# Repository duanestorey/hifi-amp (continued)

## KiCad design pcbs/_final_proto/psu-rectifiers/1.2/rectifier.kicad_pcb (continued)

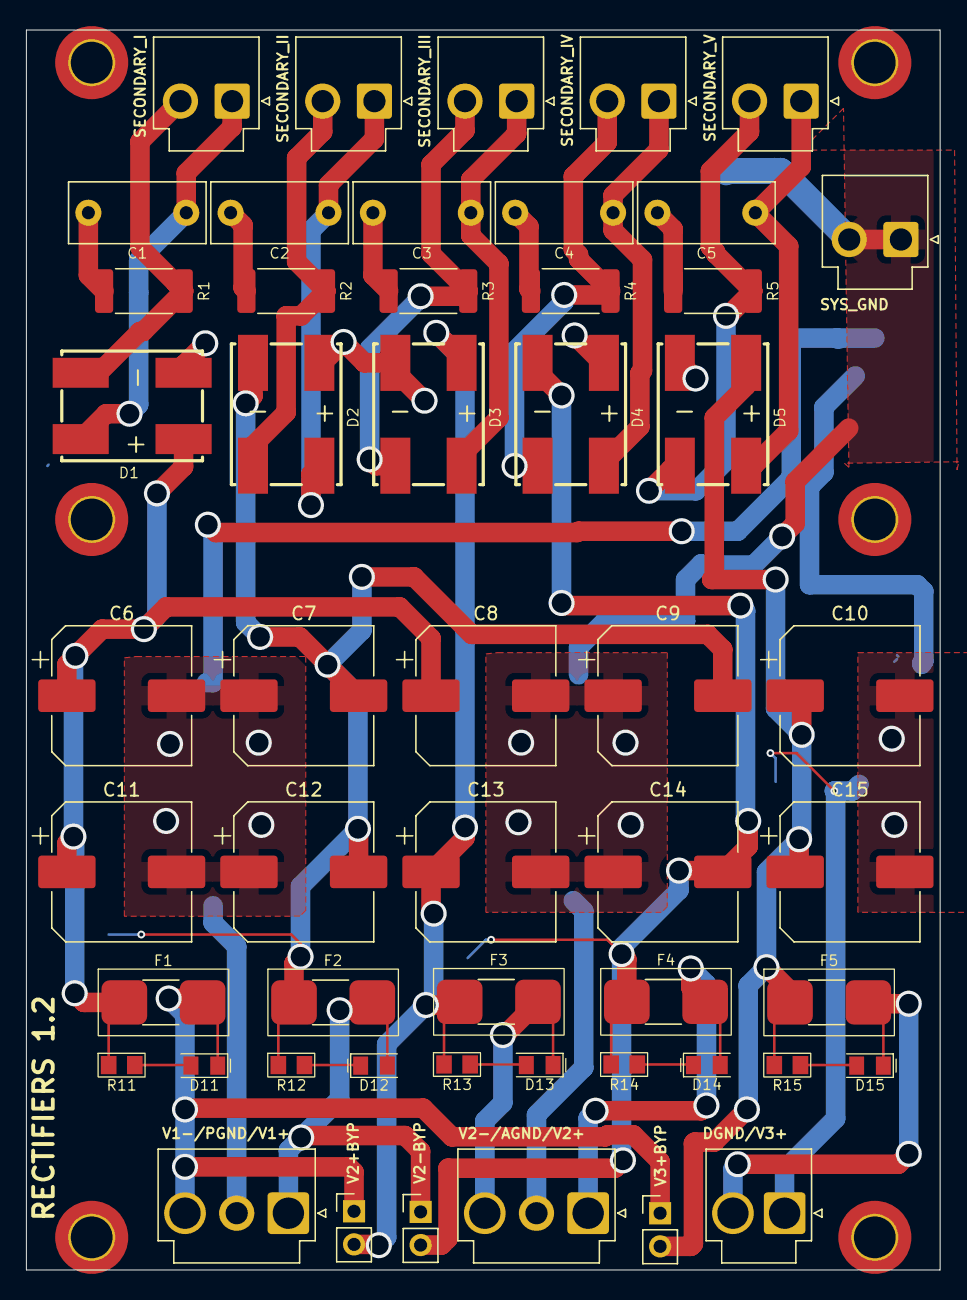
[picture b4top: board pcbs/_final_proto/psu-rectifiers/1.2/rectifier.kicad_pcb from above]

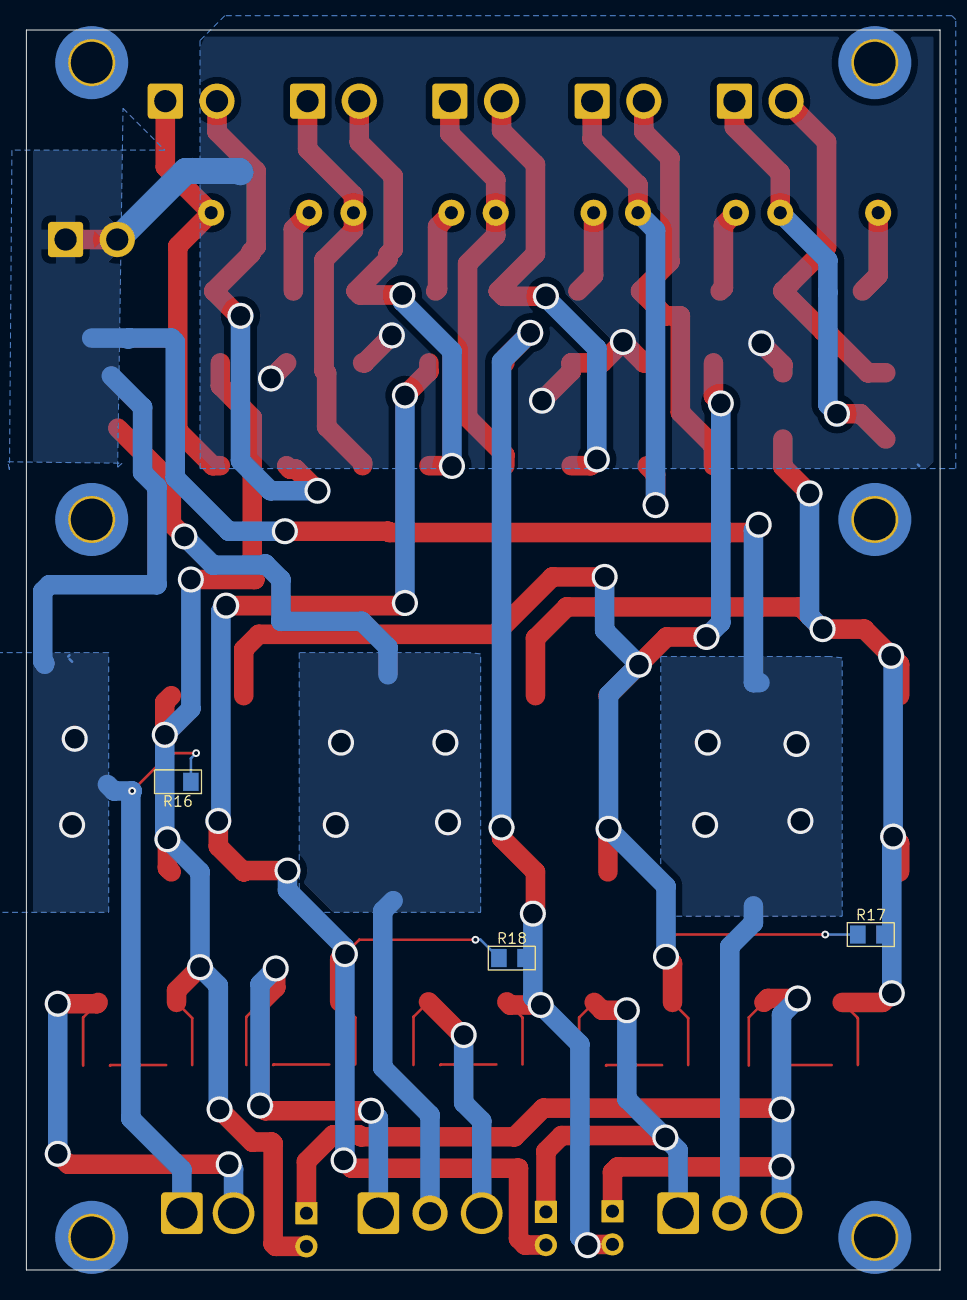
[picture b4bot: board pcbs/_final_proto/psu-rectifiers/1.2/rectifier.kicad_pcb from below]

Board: 2 copper layers, 70.0 x 95.0 mm, 61 parts (3 on the bottom side), 31 nets.

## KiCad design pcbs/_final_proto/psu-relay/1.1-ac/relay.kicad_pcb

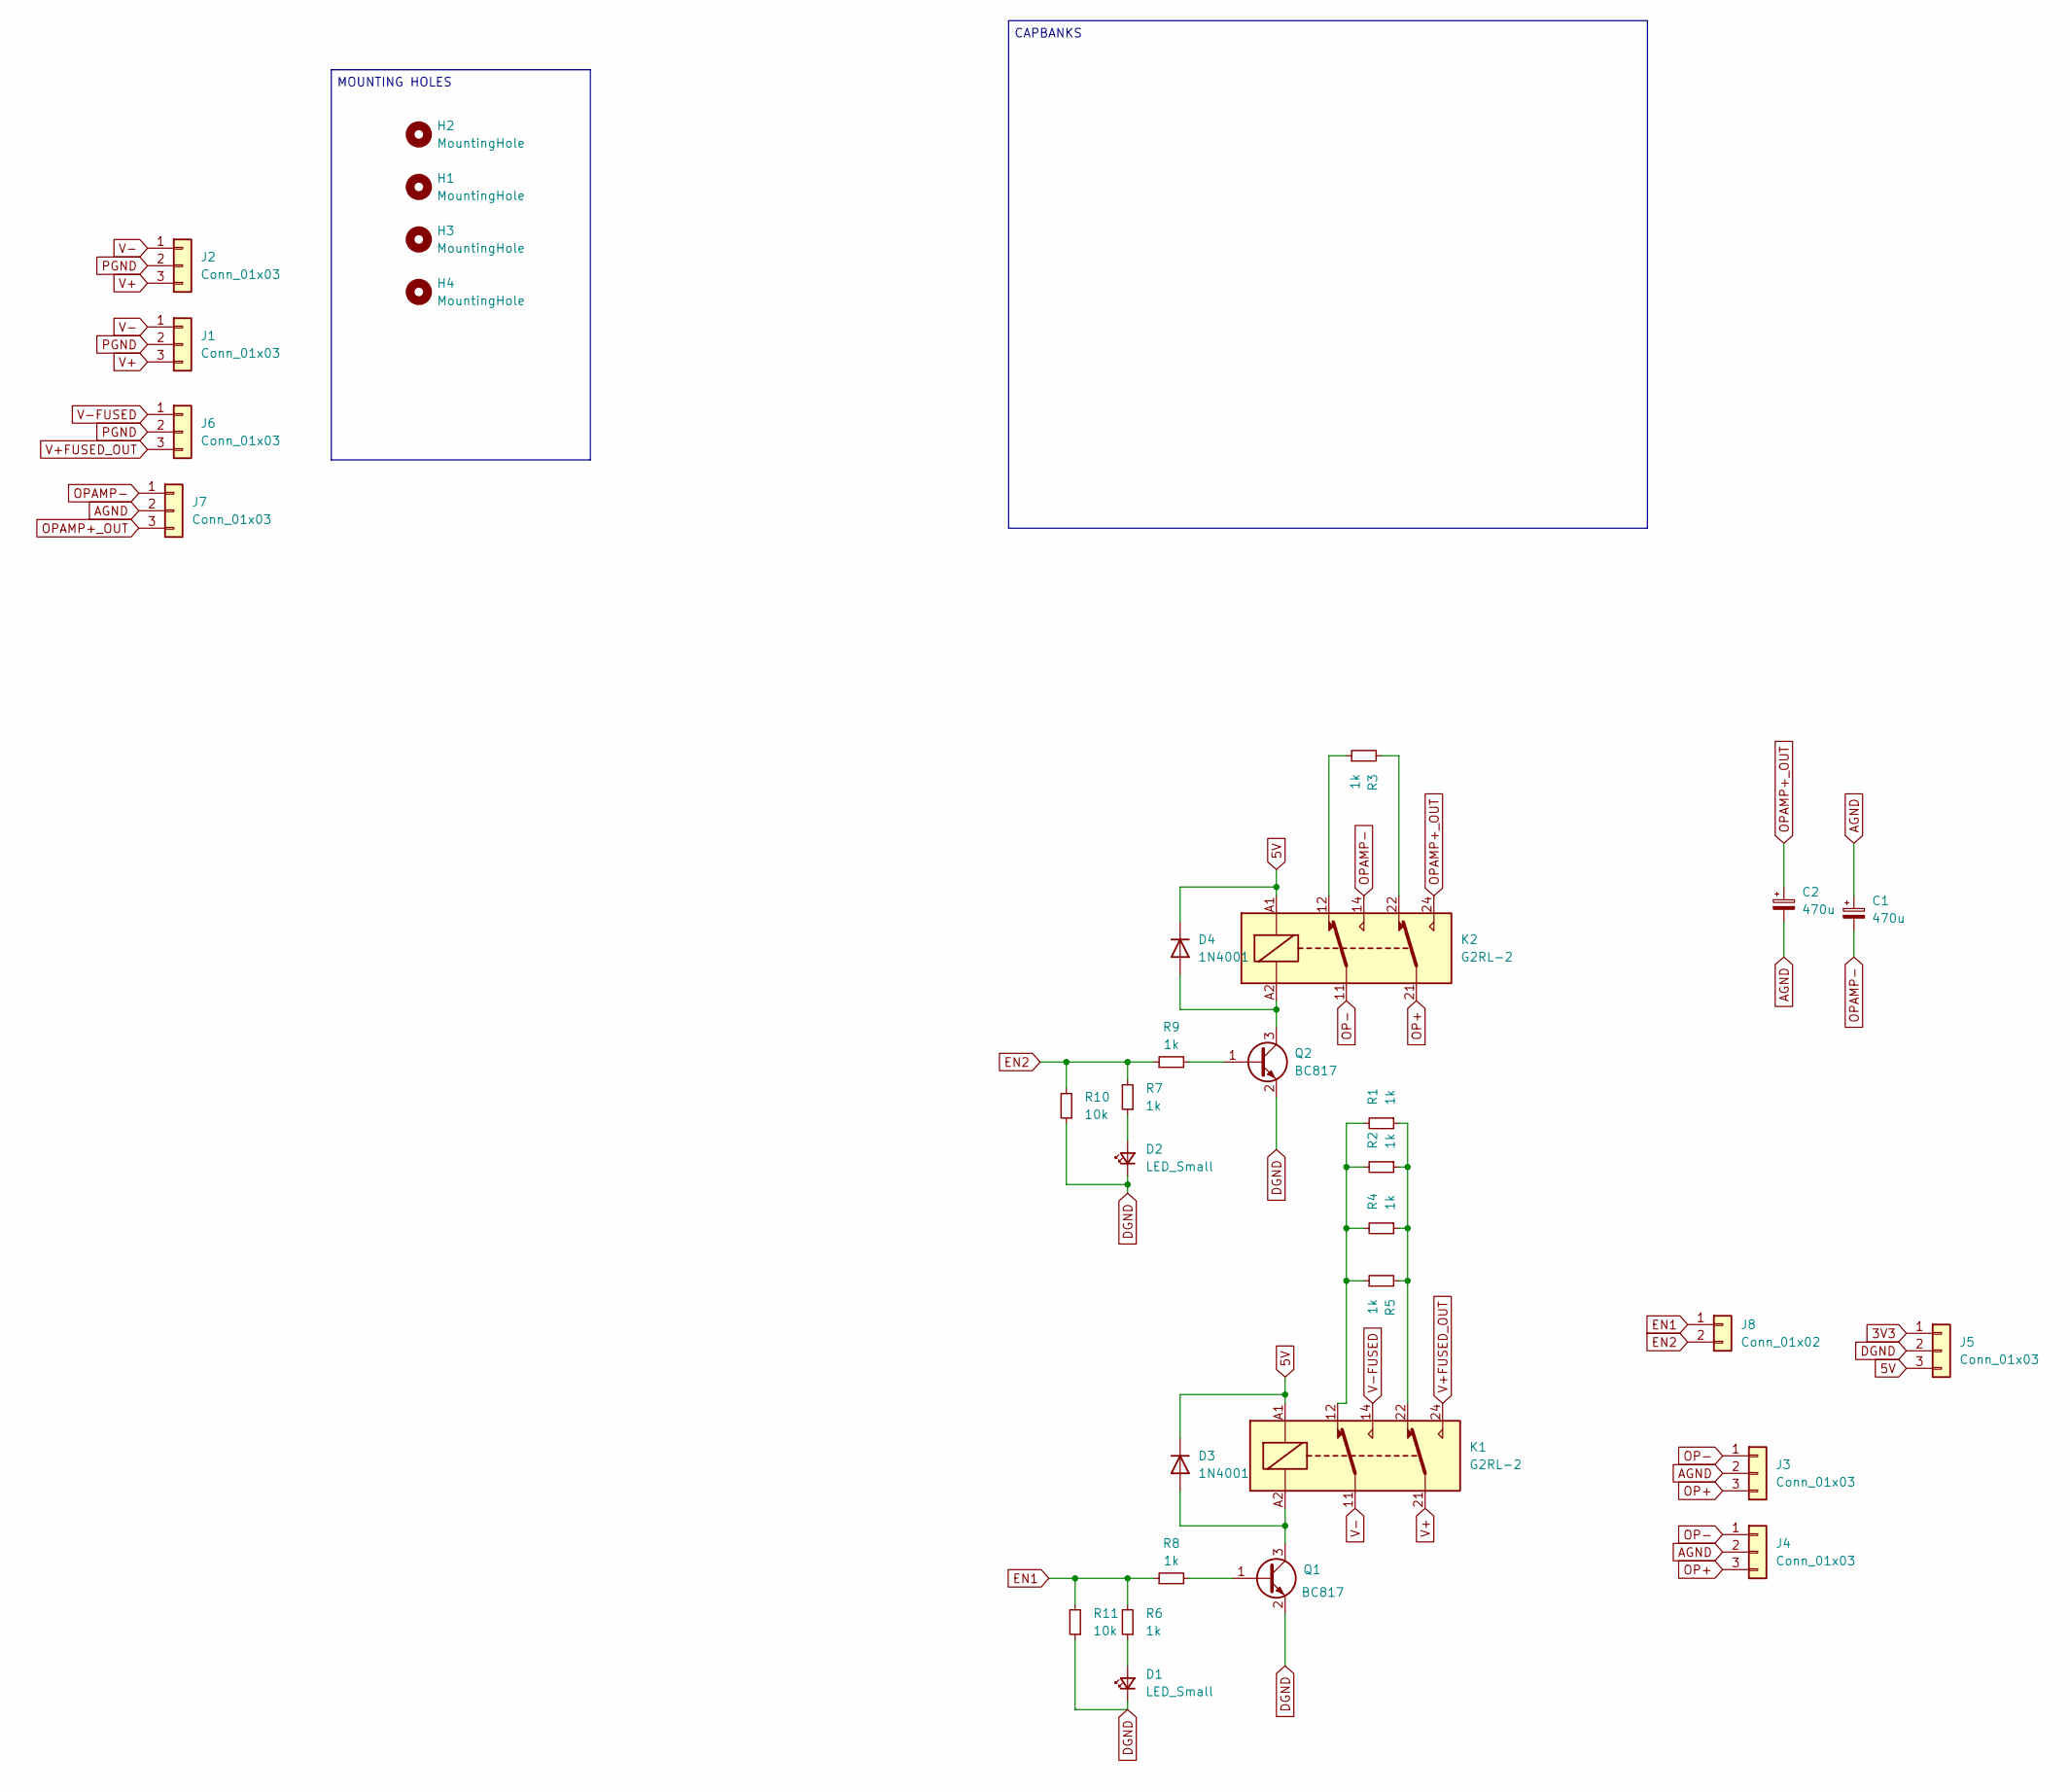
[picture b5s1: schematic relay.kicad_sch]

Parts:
C1, C2: 470u; CP_Elec_6.3x7.7
D1, D2: LED_Small; LED_0805_2012Metric_Pad_HandSolder_Duane
D3, D4: 1N4001; D_SMA
H1, H2, H3, H4: MountingHole; MountingHole_3.2mm_M3_DIN965_Pad_TopBottom
J1, J2, J6, J7: Conn_01x03; JST_VH_B3P-VH-B_1x03_P3.96mm_Vertical_Duane
J3, J4, J5: Conn_01x03; JST_PH_B3B-PH-K_1x03_P2.00mm_Vertical
J8: Conn_01x02; JST_PH_B2B-PH-K_1x02_P2.00mm_Vertical
K1, K2: G2RL-2; Relay_DPDT_Omron_G2RL-2
Q1, Q2: BC817; SOT-23
R1, R2, R4, R5: 1k; R_2512_6332Metric_Pad1.40x3.35mm_HandSolder
R3: 1k; R_1206_3216Metric_Pad1.30x1.75mm_HandSolder_Duane
R6, R7, R8, R9: 1k; R_0805_2012Metric_Pad1.20x1.40mm_HandSolder_Duane
R10, R11: 10k; R_0805_2012Metric_Pad1.20x1.40mm_HandSolder_Duane

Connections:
3V3: J5.1
5V: D3.1 (K), D4.1 (K), J5.3, K1.A1, K2.A1
AGND: C1.1, C2.2, J3.2, J4.2, J7.2
DGND: D1.1 (K), D2.1 (K), J5.2, Q1.2 (E), Q2.2 (E), R10.1, R11.1
EN1: J8.1, R6.2, R8.1, R11.2
EN2: J8.2, R7.2, R9.1, R10.2
unnamed: D1.2 (A), R6.1
unnamed: D2.2 (A), R7.1
unnamed: D3.2 (A), K1.A2, Q1.3 (C)
unnamed: D4.2 (A), K2.A2, Q2.3 (C)
unnamed: K1.12, R1.2, R2.2, R4.2, R5.1
unnamed: K1.22, R1.1, R2.1, R4.1, R5.2
unnamed: K2.12, R3.1
unnamed: K2.22, R3.2
unnamed: Q1.1 (B), R8.2
unnamed: Q2.1 (B), R9.2
OP+: J3.3, J4.3, K2.21
OP-: J3.1, J4.1, K2.11
OPAMP+_OUT: C2.1, J7.3, K2.24
OPAMP-: C1.2, J7.1, K2.14
PGND: J1.2, J2.2, J6.2
V+: J1.3, J2.3, K1.21
V+FUSED_OUT: J6.3, K1.24
V-: J1.1, J2.1, K1.11
V-FUSED: J6.1, K1.14

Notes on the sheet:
MOUNTING HOLES
CAPBANKS

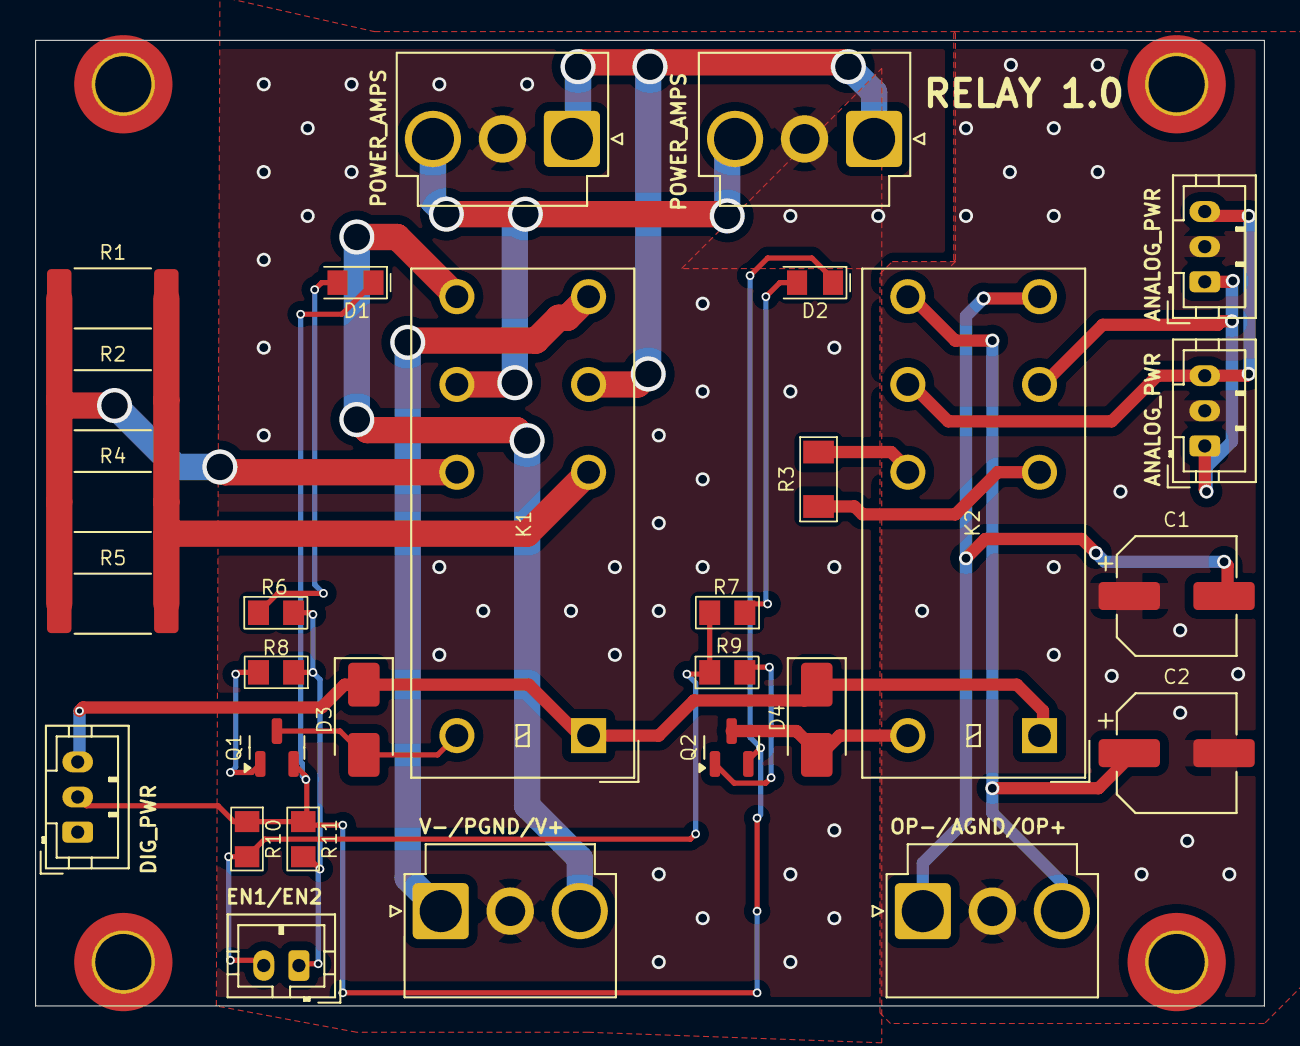
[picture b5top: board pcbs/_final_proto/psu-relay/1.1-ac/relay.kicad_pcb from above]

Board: 2 copper layers, 70.0 x 55.0 mm, 33 parts (0 on the bottom side), 24 nets.

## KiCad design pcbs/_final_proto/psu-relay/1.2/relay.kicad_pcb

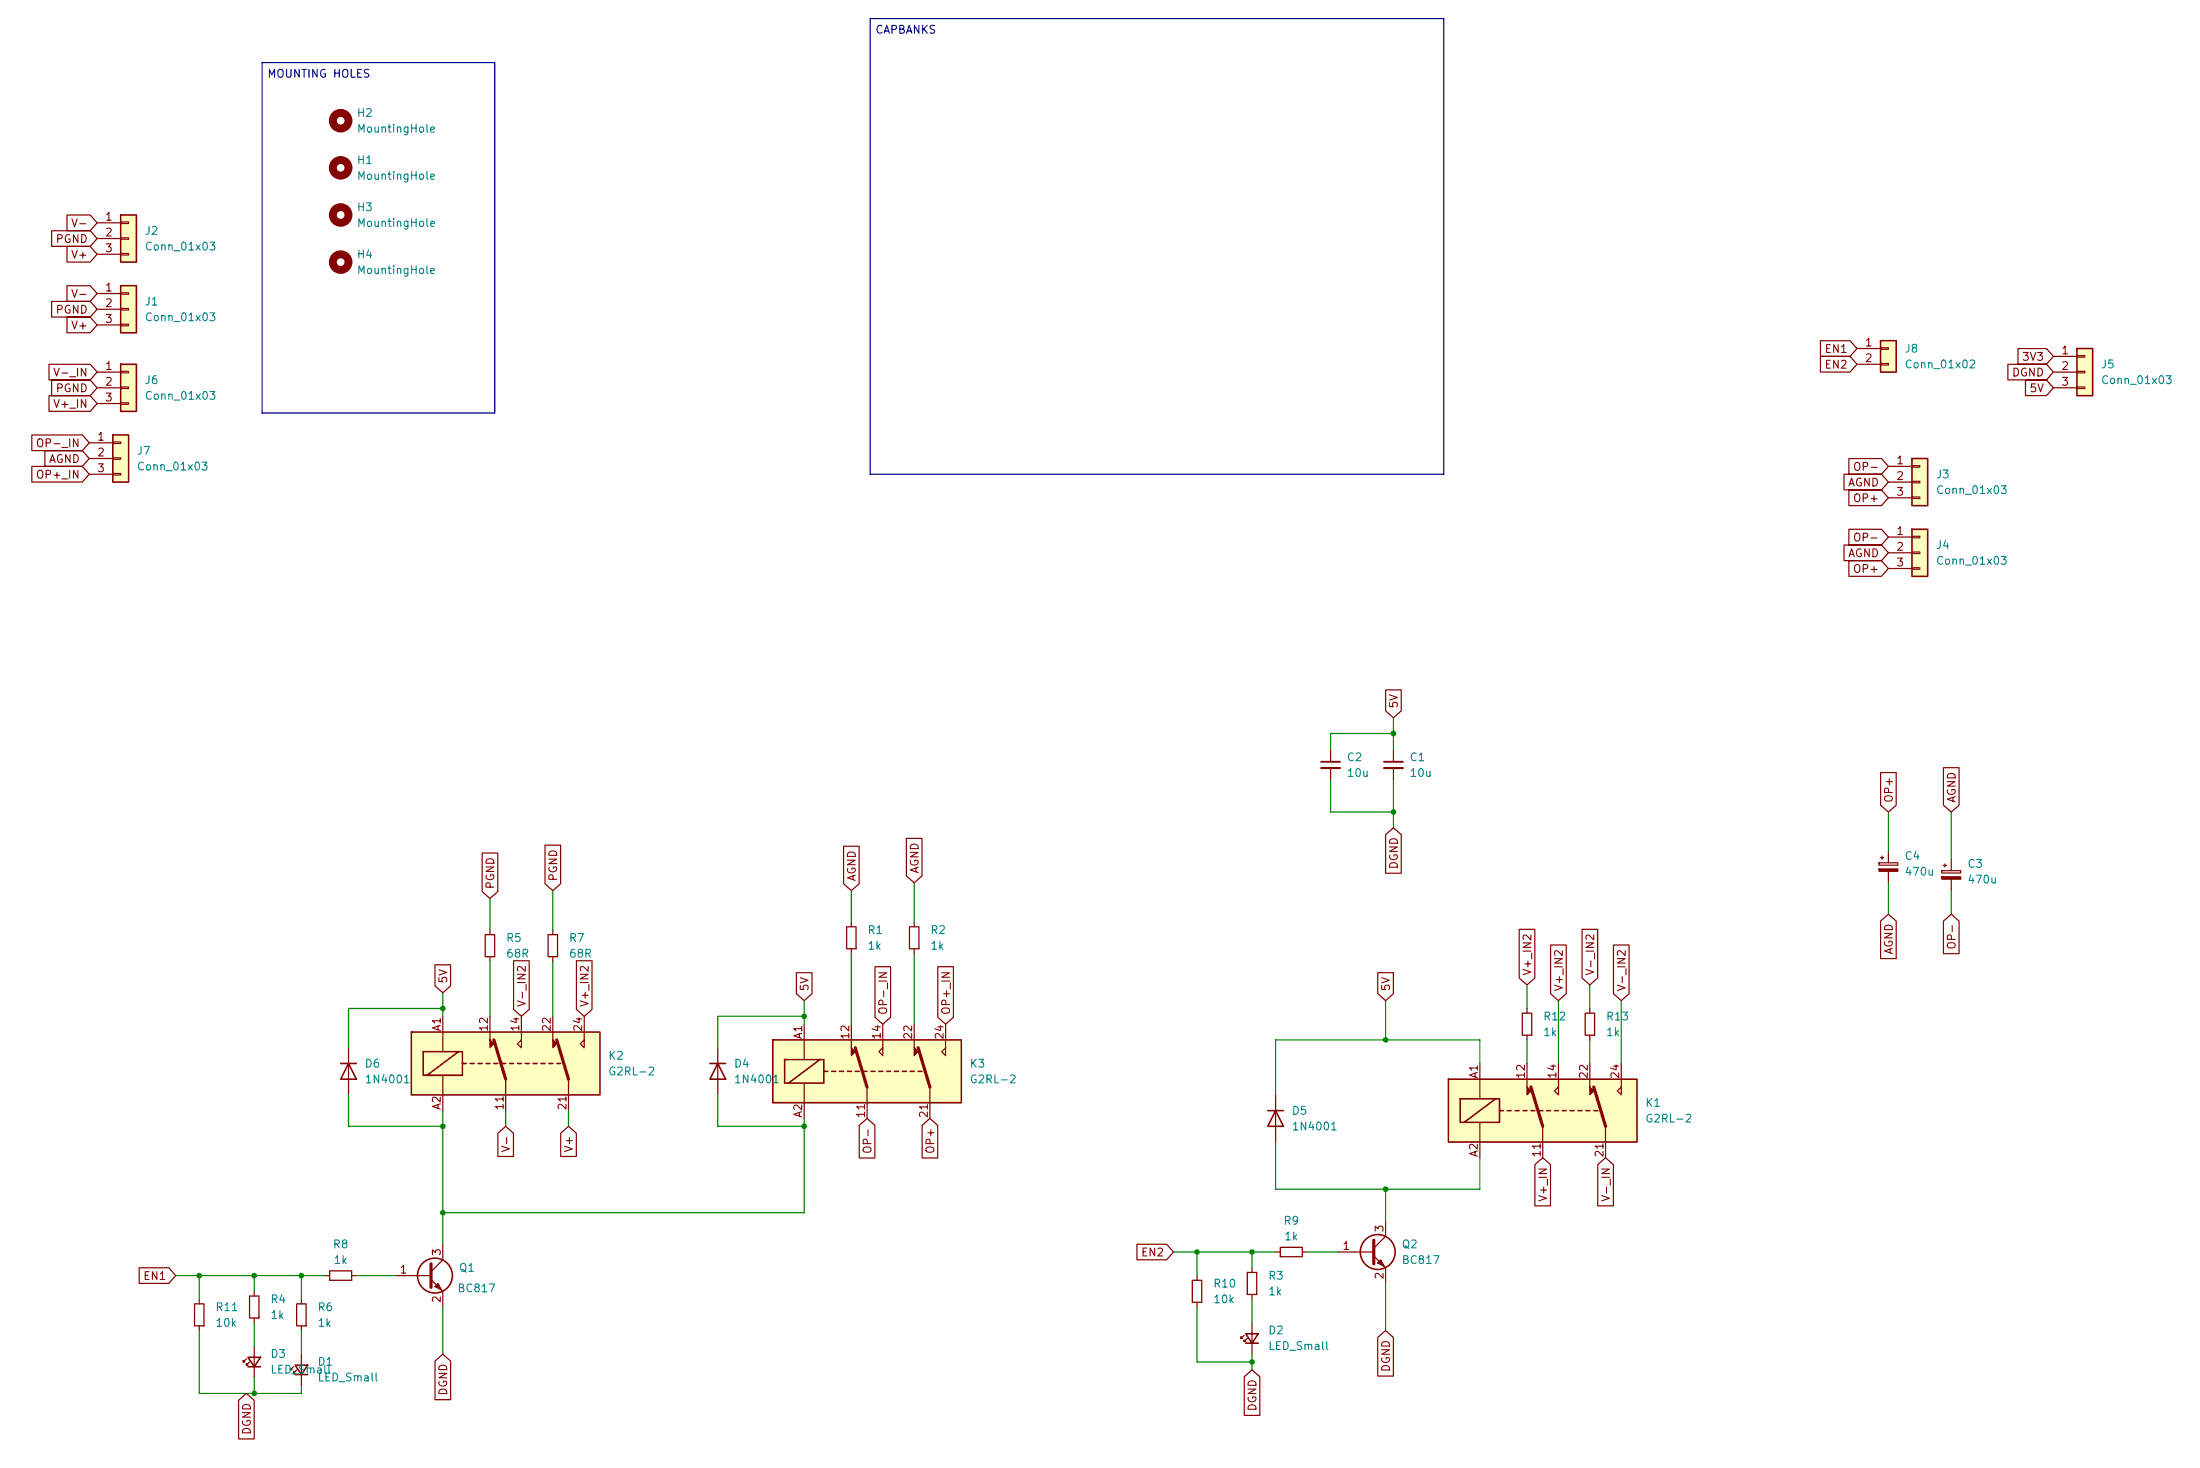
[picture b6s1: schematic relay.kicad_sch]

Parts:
C1, C2: 10u; C_1206_3216Metric_Pad1.33x1.80mm_HandSolder_Duane
C3, C4: 470u; CP_Elec_6.3x7.7
D1, D2, D3: LED_Small; LED_0805_2012Metric_Pad_HandSolder_Duane
D4, D5, D6: 1N4001; D_SMA
H1, H2, H3, H4: MountingHole; MountingHole_3.2mm_M3_DIN965_Pad_TopBottom
J1, J2, J6, J7: Conn_01x03; JST_VH_B3P-VH-B_1x03_P3.96mm_Vertical_Duane
J3, J4, J5: Conn_01x03; JST_PH_B3B-PH-K_1x03_P2.00mm_Vertical
J8: Conn_01x02; JST_PH_B2B-PH-K_1x02_P2.00mm_Vertical
K1, K2, K3: G2RL-2; Relay_DPDT_Omron_G2RL-2
Q1, Q2: BC817; SOT-23
R1, R2: 1k; R_1206_3216Metric_Pad1.30x1.75mm_HandSolder_Duane
R3, R4, R6, R8, R9: 1k; R_0805_2012Metric_Pad1.20x1.40mm_HandSolder_Duane
R5, R7: 68R; R_2512_6332Metric_Pad1.40x3.35mm_HandSolder; Mouser 279-352268RJT
R10, R11: 10k; R_0805_2012Metric_Pad1.20x1.40mm_HandSolder_Duane
R12, R13: 1k; R_2512_6332Metric_Pad1.40x3.35mm_HandSolder

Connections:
3V3: J5.1
5V: C1.1, C2.1, D4.1 (K), D5.1 (K), D6.1 (K), J5.3, K1.A1, K2.A1, K3.A1
AGND: C3.1, C4.2, J3.2, J4.2, J7.2, R1.2, R2.2
DGND: C1.2, C2.2, D1.1 (K), D2.1 (K), D3.1 (K), J5.2, Q1.2 (E), Q2.2 (E), R10.1, R11.1
EN1: J8.1, R4.2, R6.2, R8.1, R11.2
EN2: J8.2, R3.2, R9.1, R10.2
unnamed: D1.2 (A), R6.1
unnamed: D2.2 (A), R3.1
unnamed: D3.2 (A), R4.1
unnamed: D4.2 (A), D6.2 (A), K2.A2, K3.A2, Q1.3 (C)
unnamed: D5.2 (A), K1.A2, Q2.3 (C)
unnamed: K1.12, R12.1
unnamed: K1.22, R13.1
unnamed: K2.12, R5.1
unnamed: K2.22, R7.1
unnamed: K3.12, R1.1
unnamed: K3.22, R2.1
unnamed: Q1.1 (B), R8.2
unnamed: Q2.1 (B), R9.2
OP+: C4.1, J3.3, J4.3, K3.21
OP+_IN: J7.3, K3.24
OP-: C3.2, J3.1, J4.1, K3.11
OP-_IN: J7.1, K3.14
PGND: J1.2, J2.2, J6.2, R5.2, R7.2
V+: J1.3, J2.3, K2.21
V+_IN: J6.3, K1.11
V+_IN2: K1.14, K2.24, R12.2
V-: J1.1, J2.1, K2.11
V-_IN: J6.1, K1.21
V-_IN2: K1.24, K2.14, R13.2

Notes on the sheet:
MOUNTING HOLES
CAPBANKS

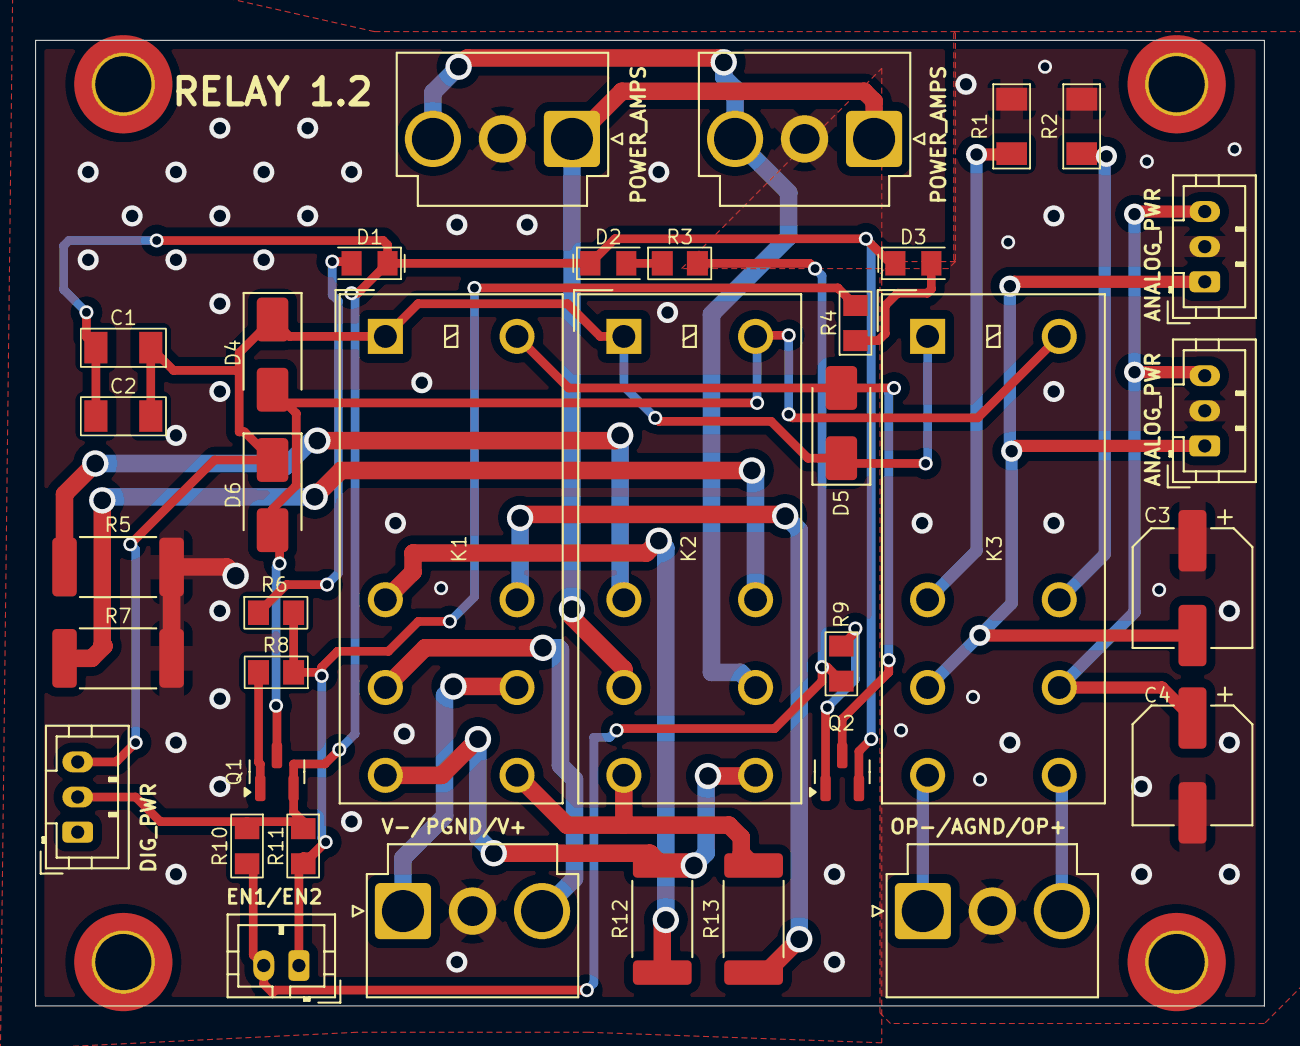
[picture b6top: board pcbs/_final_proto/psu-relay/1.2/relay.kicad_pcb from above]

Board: 2 copper layers, 70.0 x 55.0 mm, 40 parts (0 on the bottom side), 29 nets.

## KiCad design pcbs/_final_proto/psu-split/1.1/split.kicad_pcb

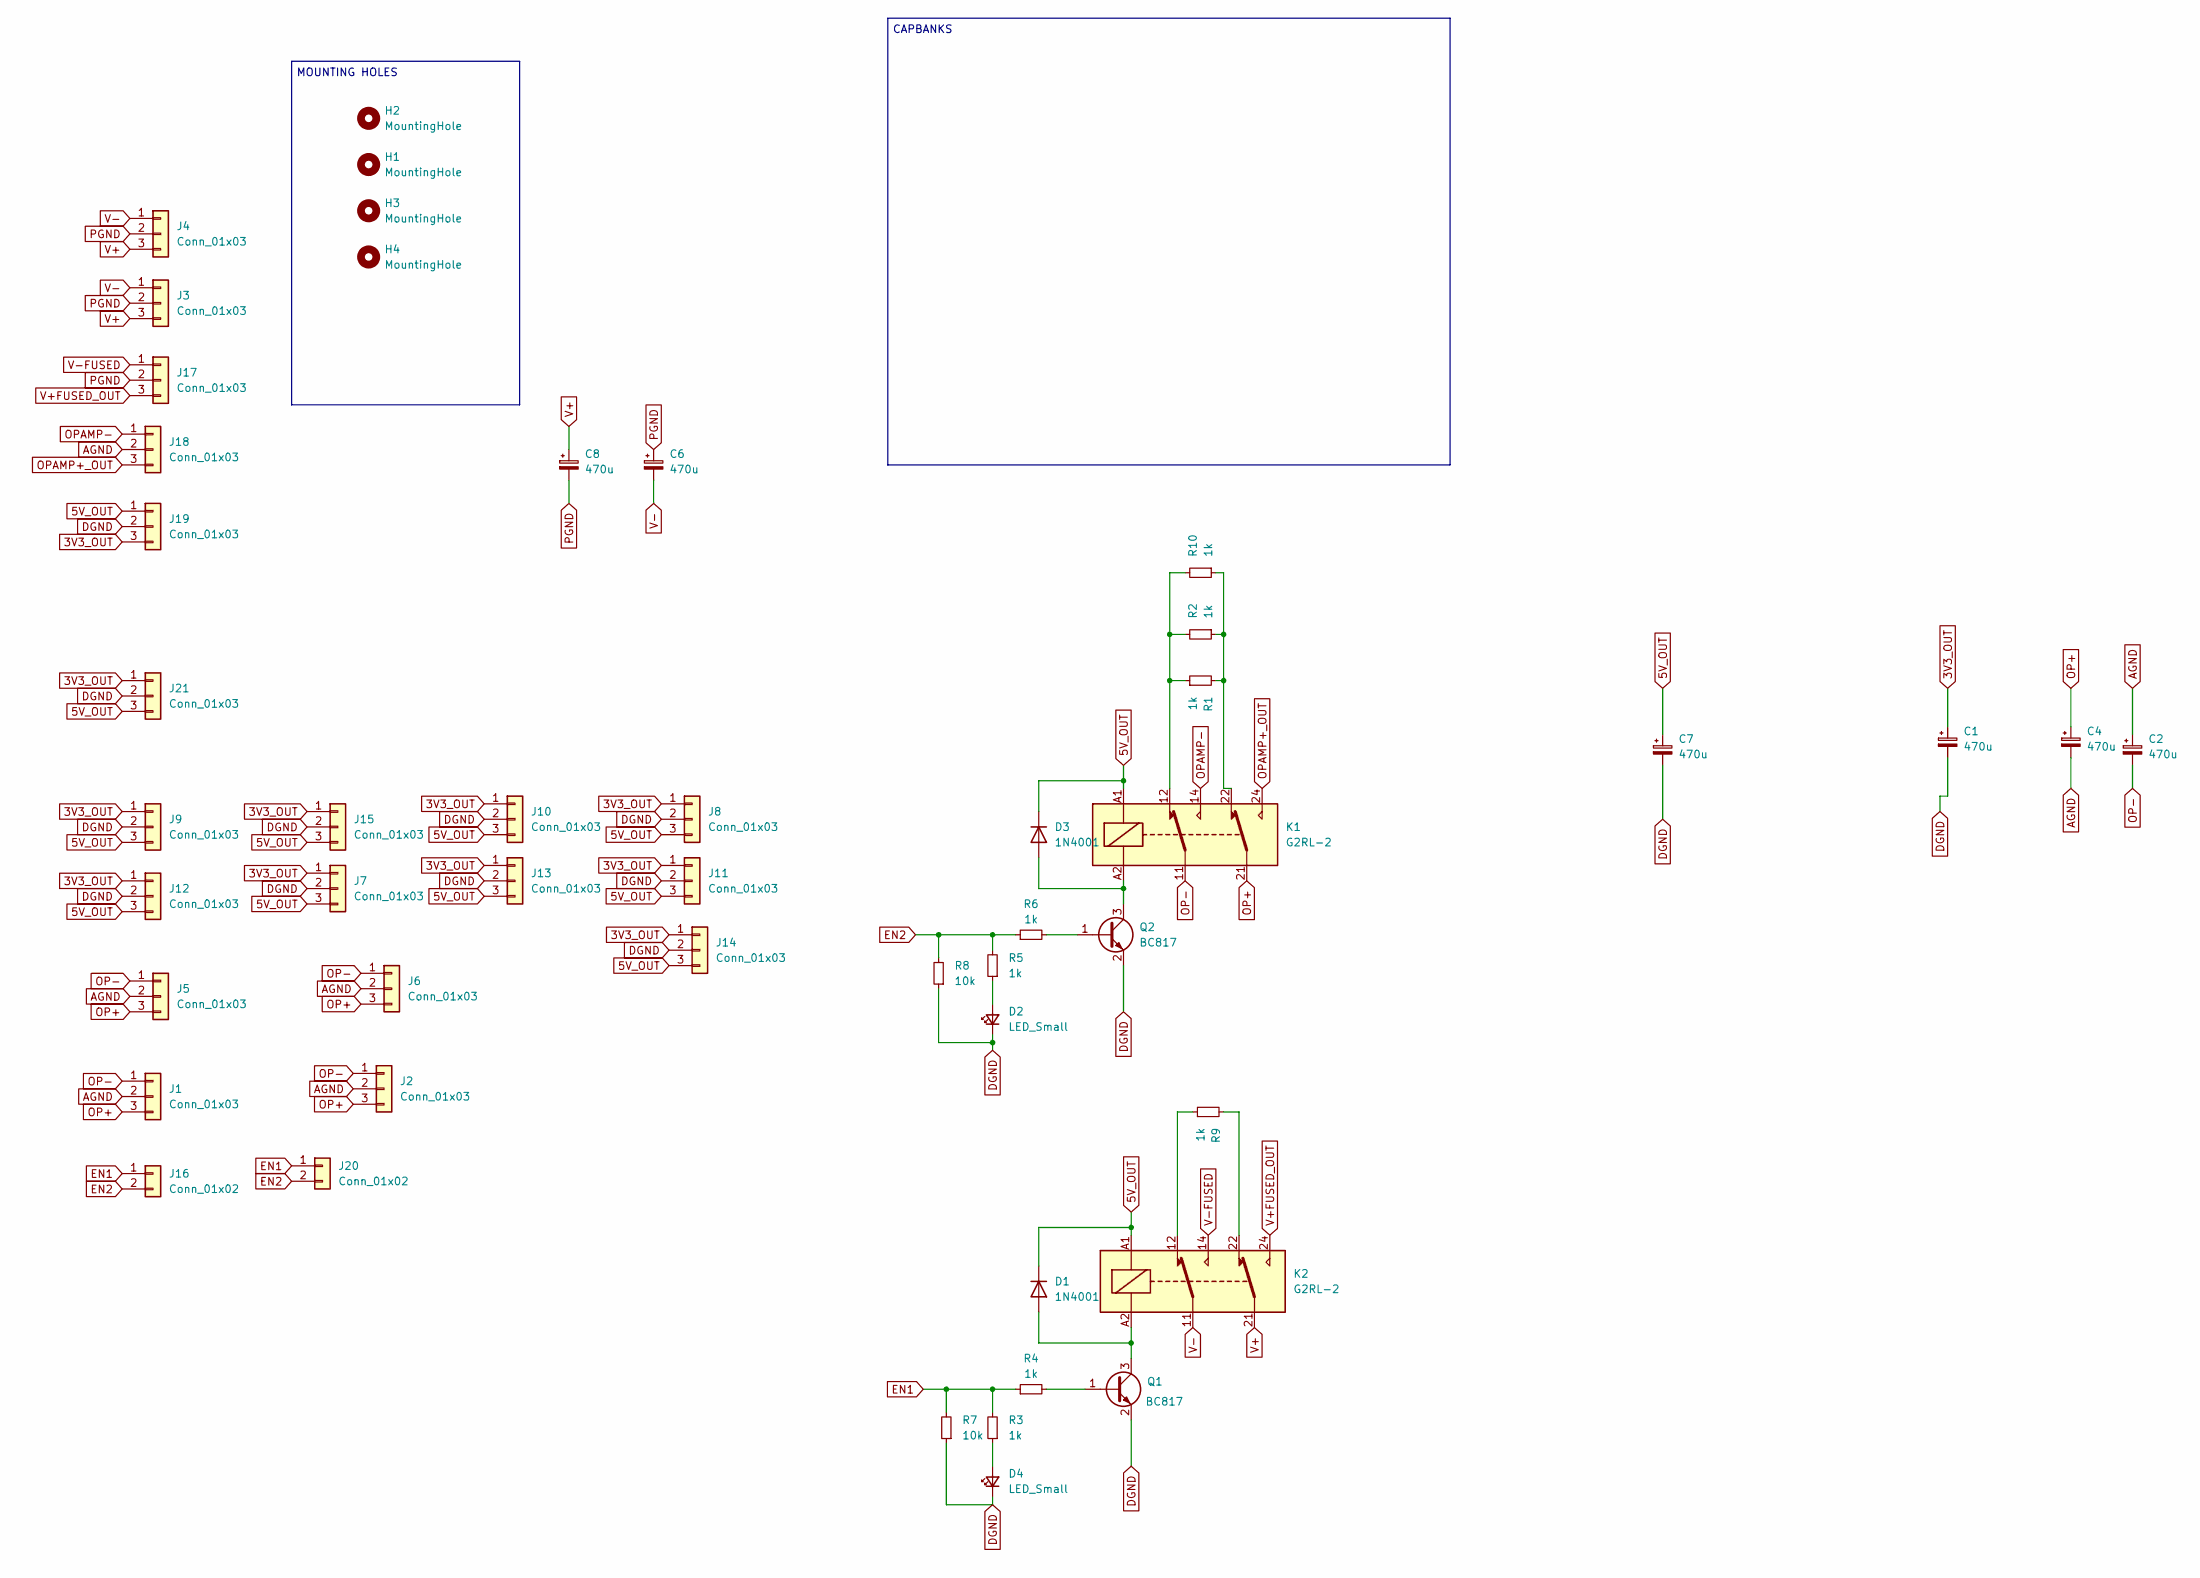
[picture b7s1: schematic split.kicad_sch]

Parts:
C1, C2, C4, C6, C7, C8: 470u; CP_Elec_6.3x7.7
D1, D3: 1N4001; D_SMA
D2, D4: LED_Small; LED_0805_2012Metric_Pad_HandSolder_Duane
H1, H2, H3, H4: MountingHole; MountingHole_3.2mm_M3_DIN965_Pad_TopBottom
J1, J2, J5, J6, J7, J8, J9, J10, J11, J12, J13, J14, J15, J21: Conn_01x03; JST_PH_B3B-PH-K_1x03_P2.00mm_Vertical
J3, J4, J17, J18, J19: Conn_01x03; JST_VH_B3P-VH-B_1x03_P3.96mm_Vertical_Duane
J16: Conn_01x02; PinHeader_1x02_P2.54mm_Vertical
J20: Conn_01x02; JST_PH_B2B-PH-K_1x02_P2.00mm_Vertical
K1, K2: G2RL-2; Relay_DPDT_Omron_G2RL-2
Q1, Q2: BC817; SOT-23
R1: 1k; R_2512_6332Metric
R2: 1k; R_2512_6332Metric_Pad1.40x3.35mm_HandSolder
R3, R4, R5, R6: 1k; R_0805_2012Metric_Pad1.20x1.40mm_HandSolder_Duane
R7, R8: 10k; R_0805_2012Metric_Pad1.20x1.40mm_HandSolder_Duane
R9, R10: 1k; R_1206_3216Metric_Pad1.30x1.75mm_HandSolder_Duane

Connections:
3V3_OUT: C1.1, J7.1, J8.1, J9.1, J10.1, J11.1, J12.1, J13.1, J14.1, J15.1, J19.3, J21.1
5V_OUT: C7.1, D1.1 (K), D3.1 (K), J7.3, J8.3, J9.3, J10.3, J11.3, J12.3, J13.3, J14.3, J15.3, J19.1, J21.3, K1.A1, K2.A1
AGND: C2.1, C4.2, J1.2, J2.2, J5.2, J6.2, J18.2
DGND: C1.2, C7.2, D2.1 (K), D4.1 (K), J7.2, J8.2, J9.2, J10.2, J11.2, J12.2, J13.2, J14.2, J15.2, J19.2, J21.2, Q1.2 (E), Q2.2 (E), R7.1, R8.1
EN1: J16.1, J20.1, R3.2, R4.1, R7.2
EN2: J16.2, J20.2, R5.2, R6.1, R8.2
unnamed: D1.2 (A), K2.A2, Q1.3 (C)
unnamed: D2.2 (A), R5.1
unnamed: D3.2 (A), K1.A2, Q2.3 (C)
unnamed: D4.2 (A), R3.1
unnamed: K1.12, R1.1, R2.2, R10.2
unnamed: K1.22, R1.2, R2.1, R10.1
unnamed: K2.12, R9.1
unnamed: K2.22, R9.2
unnamed: Q1.1 (B), R4.2
unnamed: Q2.1 (B), R6.2
OP+: C4.1, J1.3, J2.3, J5.3, J6.3, K1.21
OP-: C2.2, J1.1, J2.1, J5.1, J6.1, K1.11
OPAMP+_OUT: J18.3, K1.24
OPAMP-: J18.1, K1.14
PGND: C6.1, C8.2, J3.2, J4.2, J17.2
V+: C8.1, J3.3, J4.3, K2.21
V+FUSED_OUT: J17.3, K2.24
V-: C6.2, J3.1, J4.1, K2.11
V-FUSED: J17.1, K2.14

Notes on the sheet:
MOUNTING HOLES
CAPBANKS

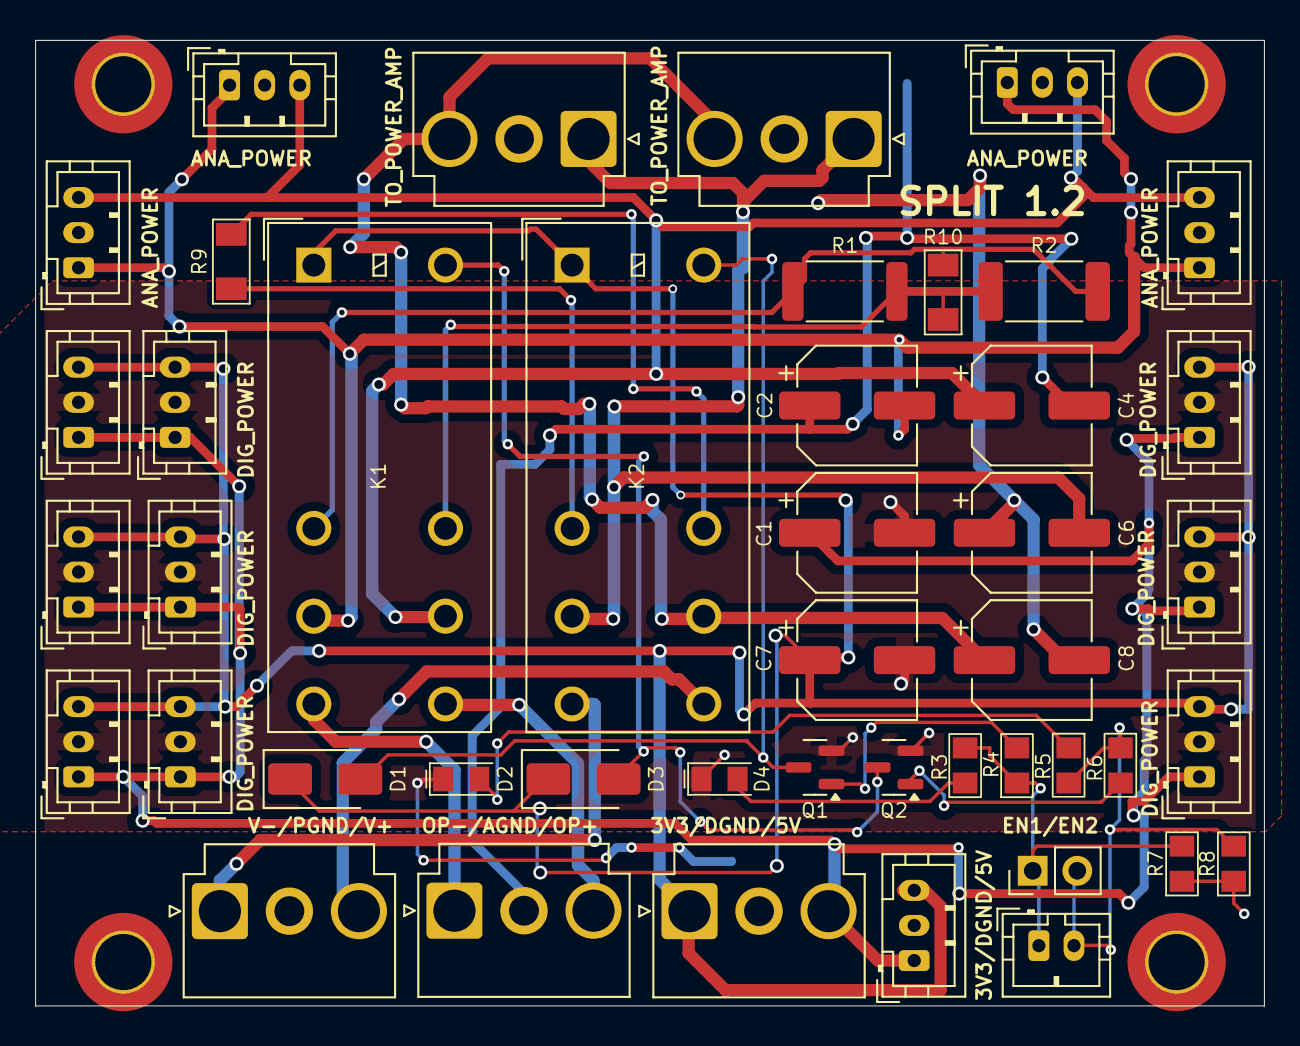
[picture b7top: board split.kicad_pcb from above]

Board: 2 copper layers, 70.0 x 55.0 mm, 49 parts (0 on the bottom side), 25 nets.
